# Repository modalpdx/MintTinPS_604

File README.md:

#MintTinPS_604

A simple power supply board for "standard" mint tins. Examples: Altoids,
Penguin Mints, Mintz. The board is sized/shaped to fit in the tin while
still allowing enough room for up to three AA batteries in an open holder
and a mini-toggle to switch the power supply on/off.

[*NOTE: In spite of the lower number in the project name, this power supply
design actually provides more current than the MintTinPS_882 design. I
recommend you go with this board instead.*]

This version of the mint tin power supply uses a [**Maxim MAX604 linear voltage regulator**](http://www.maximintegrated.com/en/products/power/linear-regulators/MAX604.html "MAX604 Info"), which gives us the following output voltage options:

* Default voltage: 3.3V
* Adjustable voltage: 1.25V to 11V

The adjustable voltage is activated by setting a jumper (ADJV). If the
jumper is open, you get 3.3V.

##Parts
* Maxim MAX604 voltage regulator (8 pin DIP)
* 8 pin DIP socket (optional, but smart)
* 0.1uF capacitor (ceramic, C2 on the board)
* 10uF capacitor (C1 on the board)
* 10k Bourns trimmer potentiometer (3306)
* 2-pin male header (2.54mm/0.1") & jumper

Optional for power connection:
* 2 x 2 male header (2.54mm/0.1"), right-angled 
* Two 1 x 2 female headers (2.54mm/0.1") for power wires

Other:
* "Standard" size mint tin (ex: large Altoids/Mintz/Penguin Mints tin)
* .125" spacers (I'm guessing adhesive, nylon) if spacers are your thing
* Something else to fully insulate the bottom of the board

##Setting the adjustable voltage

The level of the adjustable voltage is set with a trimmer potentiometer on
the board. Connect the output power wires (POW|out) to a multimeter, set
the multimeter to read DC voltage, then turn the potentiometer until you
have your desired voltage. You are limited by the voltage that is put out
by your batteries (there is no boost circuitry in this power supply).
Also, make sure you are not powering any components with the power supply
when you adjust the voltage.

##Implementation

I intentionally left the power connections (POW|in/out) generic so you can
connect whatever battery you wish to connect in the manner in which you'd
like to connect it, *as long as you keep in mind that your power source
has to be between 2.7V and 11.5V*. 

Until 5V goes out of fashion, I'm using a 9V battery with this. No
combination of inline AA or AAA batteries will get high enough voltage to
provide >5V and still fit in a mint tin.  When 5V goes away, three AA
batteries should work.

The use of a jumper for switching voltages was intentional. Anything that
can switch from a lower to a higher voltage should involve some user
experience "friction." If the voltage switch is exposed on the outside of
the tin, it could be accidentally bumped. Depending on what voltage was
switched to, this could result in fried components. Keeping the voltage
switching experience inside the tin makes more sense.

There are no LEDs for power status, either. Feel free to add them if you
like. I wanted all power to go to the circuit I'm designing, not
blinkenlights.

##Limitations

* Input voltage range: 2.7V to 11.5V
* Output voltage range: 1.25V to 11V (input voltage limits upper value)
* Non-adjustable voltage: 3.3V
* No voltage boost capabilities
* Maximum current: 500mA
* Linear regulators are not the most efficient

This is a perfectly capable power supply for breadboarding. If you need a
power supply for something else, this isn't it. 

##Motivation

I wanted to have a small breadboard/power supply combo that would be
compact, self-contained, and offer two voltages. There are projects on the
Internet that do this already but they either skimp on the voltages (only
offer one, typically 5V) or they default to 5V and 9V (I have never needed
9V on a breadboard before, and I probably never will). 

I also wanted to future-proof the power supply.
Right now the common component voltages seem to be 3.3V and 5V, but 5V
components are becoming less common. It makes more sense to have a power
supply that offers 3.3V plus one adjustable voltage, so when 5V goes away,
I'll still have 3.3V and one other up-and-coming voltage (looks like 2.5V
may be the next one).

##Miscellaneous Notes

If you want the power supply to default to 5V instead of 3.3V, the Maxim
MAX603 should be a drop-in replacement for the MAX604. This chip would
give you everything the MAX604 offers but the non-adjustable voltage would
be 5V. The adjustable voltage is handled identically to the MAX604.

The .brd file was run through OSHPark's design rules. It has not been run
through DirtyPCB's design rules. If you're building boards through
DirtyPCBs and want to upload the .brd file by itself, you should probably
run it through Eagle and DirtyPCB's design rules first. Or just submit the
gerbers instead. Your call.

The first run of PCBs from OSHPark has been received and tested and they
work great. Have at it.

##VERSIONS

0.1 - Initial version.

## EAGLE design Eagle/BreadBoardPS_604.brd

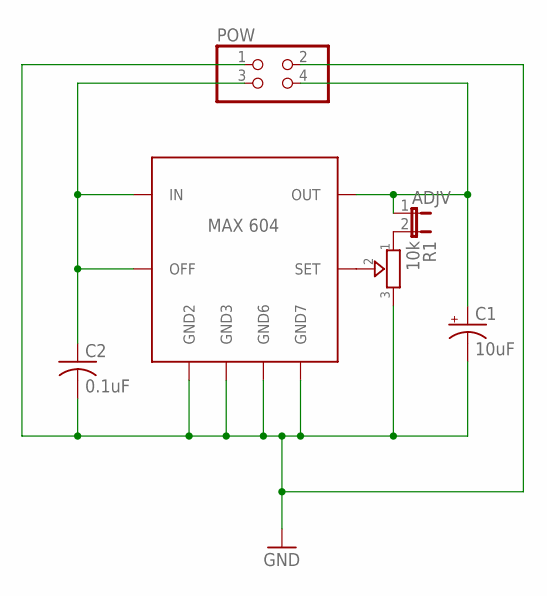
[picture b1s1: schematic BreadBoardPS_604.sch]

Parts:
ADJV: JP1E; JP1
C1: 10uF; E2,5-5
C2: 0.1uF; C025-024X044
MAX604: MAX604; DIL08
POW: PINHD-2X22X02/90NOSILK; 2X02/90
R1: 10k; TRIMMER_3306F

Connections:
GND: C1.-, C2.2, MAX604.2 (GND2), MAX604.3 (GND3), MAX604.6 (GND6), MAX604.7 (GND7), POW.1, POW.2, R1.3
unnamed: C2.1, MAX604.1 (IN), MAX604.4 (OFF), POW.3
unnamed: ADJV.2, R1.1
unnamed: MAX604.5 (SET), R1.2
unnamed: ADJV.1, C1.+, MAX604.8 (OUT), POW.4

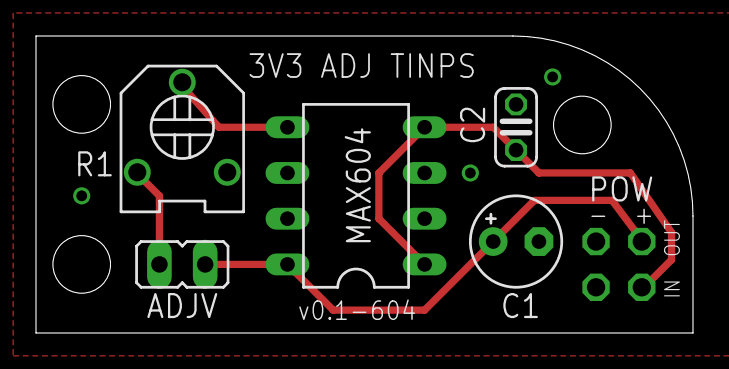
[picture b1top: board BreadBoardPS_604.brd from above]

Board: 2 copper layers, 36.5 x 16.5 mm, 6 parts (0 on the bottom side), 5 nets.

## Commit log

2014-12-09 Initial checkin. Only OSHPark gerbers this time.
2014-12-09 Updated README.
2014-12-09 Typo
2014-12-09 PDF of the schematic.
2014-12-10 Added spacers to the parts list
2014-12-20 Added DirtyPCBs gerbers.
2014-12-20 Updated parts list (broken down differently). Note about OSHPark boards not being tested and note about DirtyPCBs design rules.
2014-12-20 Added version info.
2014-12-20 Added note about PCB testing (success).
2014-12-22 Image of built PS.
